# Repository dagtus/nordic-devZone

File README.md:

# nordic-devZone
Share files with support teams

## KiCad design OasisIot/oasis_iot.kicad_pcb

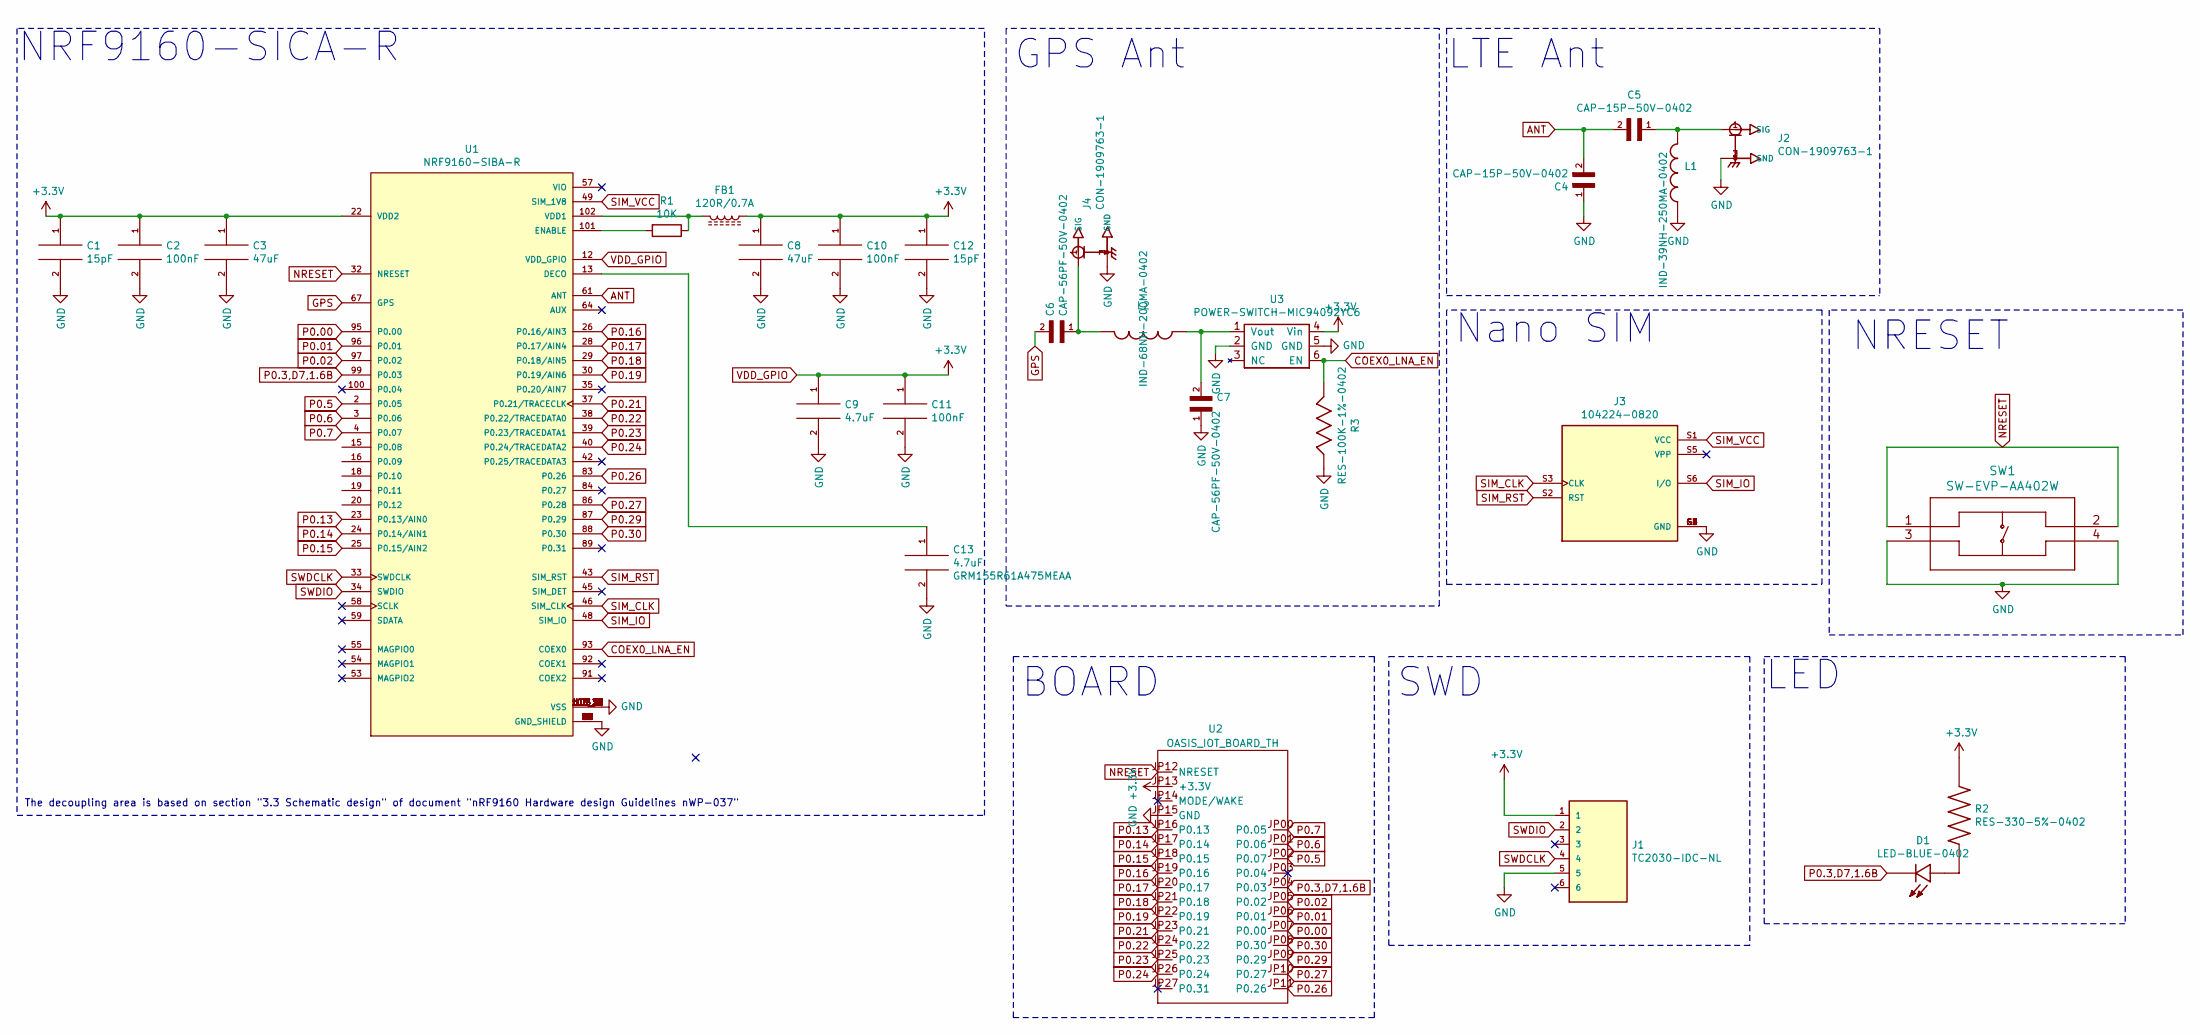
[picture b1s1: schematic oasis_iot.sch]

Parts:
C1, C12: 15pF; C_0201_0603Metric; Part Number GJM0335C1E150JB01
C2, C10, C11: 100nF; C_0201_0603Metric; Part Number GRM033R61A104KE15
C3, C8: 47uF; C_0805_2012Metric; Part Number GRM21BR61A476ME15
C4, C5: CAP-15P-50V-0402; CAPC1005X55N
C6, C7: CAP-56PF-50V-0402; CAPC1005X55N
C9, C13: 4.7uF; C_0402_1005Metric; Part Number GRM155R61A475MEAA
D1: LED-BLUE-0402; EAST10052BA0; PARTREV 3
FB1: 120R/0.7A; L_0402_1005Metric; Part number BLM15AX121SN1
J1: TC2030-IDC-NL; TAG_TC2030-IDC-NL; PARTREV MS
J2, J4: CON-1909763-1; TE_1909763-1
J3: 104224-0820; MOLEX_104224-0820; PARTREV A
L1: IND-39NH-250MA-0402; LQG15HN39NJ02D
L2: IND-68NH-200MA-0402; INDC1005X55N
R1: 10K; R_0201_0603Metric; Part Number RC0201FR-0710KL
R2: RES-330-5%-0402; RC0402JR-07330RL
R3: RES-100K-1%-0402; 0402_RES
SW1: SW-EVP-AA402W; EVPAA402W
U1: NRF9160-SIBA-R; PARTREV v0.7.1
U2: OASIS_IOT_BOARD_TH; MODULE_OASIS_IOT_BOARD_TH
U3: POWER-SWITCH-MIC94092YC6; MIC94092YC6-TR

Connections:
ANT: C4.2, C5.2, U1.61 (ANT)
COEX0_LNA_EN: R3.1, U1.93 (COEX0), U3.6 (EN)
GND: C1.2, C2.2, C3.2, C4.1, C7.1, C8.2, C9.2, C10.2, C11.2, C12.2, C13.2, J1.5, J2.2 (GND), J2.3 (GND), J3.G1 (GND), J3.G2 (GND), J3.G3 (GND), J3.G4 (GND), J3.S4 (GND), J4.2 (GND), J4.3 (GND), L1.2, R3.2, SW1.3, SW1.4, U1.1 (GND_SHIELD), U1.5 (GND_SHIELD), U1.9 (GND_SHIELD), U1.14 (GND_SHIELD), U1.17 (GND_SHIELD), U1.21 (GND_SHIELD), U1.27 (GND_SHIELD), U1.31 (GND_SHIELD), U1.36 (GND_SHIELD), U1.41 (GND_SHIELD), U1.44 (GND_SHIELD), U1.47 (GND_SHIELD), U1.50 (GND_SHIELD), U1.52 (GND_SHIELD), U1.56 (GND_SHIELD), U1.60 (GND_SHIELD), U1.62 (GND_SHIELD), U1.63 (GND_SHIELD), U1.65 (GND_SHIELD), U1.66 (GND_SHIELD), U1.72 (GND_SHIELD), U1.74 (GND_SHIELD), U1.75 (GND_SHIELD), U1.76 (GND_SHIELD), U1.77 (GND_SHIELD), U1.78 (GND_SHIELD), U1.79 (GND_SHIELD), U1.80 (GND_SHIELD), U1.81 (GND_SHIELD), U1.82 (GND_SHIELD), U1.85 (GND_SHIELD), U1.90 (GND_SHIELD), U1.94 (GND_SHIELD), U1.98 (GND_SHIELD), U1.103_1 (VSS), U1.103_2 (VSS), U1.103_3 (VSS), U1.103_4 (VSS), U1.103_5 (VSS), U1.103_6 (VSS), U1.103_7 (VSS), U1.103_8 (VSS), U1.103_9 (VSS), U1.103_10 (VSS), U1.103_11 (VSS), U1.103_12 (VSS), U1.103_13 (VSS), U1.103_14 (VSS), U1.103_15 (VSS), U1.103_16 (VSS), U1.103_17 (VSS), U1.103_18 (VSS), U1.103_19 (VSS), U1.103_20 (VSS), U1.103_21 (VSS), U1.103_22 (VSS), U1.103_23 (VSS), U1.103_24 (VSS), U1.103_25 (VSS), U1.103_26 (VSS), U1.103_27 (VSS), U1.103_28 (VSS), U1.103_29 (VSS), U1.103_30 (VSS), U1.103_31 (VSS), U1.103_32 (VSS), U1.103_33 (VSS), U1.103_34 (VSS), U1.103_35 (VSS), U2.JP15 (GND), U3.2 (GND), U3.5 (GND)
GPS: C6.2, U1.67 (GPS)
NRESET: SW1.1, SW1.2, U1.32 (NRESET), U2.JP12 (NRESET)
unnamed: C5.1, J2.1 (SIG), L1.1
unnamed: C6.1, J4.1 (SIG), L2.1
unnamed: C7.2, L2.2, U3.1 (Vout)
unnamed: C13.1, U1.13 (DECO)
unnamed: D1.A, R2.2
unnamed: FB1.2, R1.1, U1.102 (VDD1)
unnamed: R1.2, U1.101 (ENABLE)
P0.00: U1.95 (P0.00), U2.JP07 (P0.00)
P0.01: U1.96 (P0.01), U2.JP06 (P0.01)
P0.02: U1.97 (P0.02), U2.JP05 (P0.02)
P0.3,D7,1.6B: D1.C, U1.99 (P0.03), U2.JP04 (P0.03)
P0.5: U1.2 (P0.05), U2.JP02 (P0.07)
P0.6: U1.3 (P0.06), U2.JP01 (P0.06)
P0.7: U1.4 (P0.07), U2.JP00 (P0.05)
P0.13: U1.23 (P0.13/AIN0), U2.JP16 (P0.13)
P0.14: U1.24 (P0.14/AIN1), U2.JP17 (P0.14)
P0.15: U1.25 (P0.15/AIN2), U2.JP18 (P0.15)
P0.16: U1.26 (P0.16/AIN3), U2.JP19 (P0.16)
P0.17: U1.28 (P0.17/AIN4), U2.JP20 (P0.17)
P0.18: U1.29 (P0.18/AIN5), U2.JP21 (P0.18)
P0.19: U1.30 (P0.19/AIN6), U2.JP22 (P0.19)
P0.21: U1.37 (P0.21/TRACECLK), U2.JP23 (P0.21)
P0.22: U1.38 (P0.22/TRACEDATA0), U2.JP24 (P0.22)
P0.23: U1.39 (P0.23/TRACEDATA1), U2.JP25 (P0.23)
P0.24: U1.40 (P0.24/TRACEDATA2), U2.JP26 (P0.24)
P0.26: U1.83 (P0.26), U2.JP11 (P0.26)
P0.27: U1.86 (P0.28), U2.JP10 (P0.27)
P0.29: U1.87 (P0.29), U2.JP09 (P0.29)
P0.30: U1.88 (P0.30), U2.JP08 (P0.30)
SIM_CLK: J3.S3 (CLK), U1.46 (SIM_CLK)
SIM_IO: J3.S6 (I/O), U1.48 (SIM_IO)
SIM_RST: J3.S2 (RST), U1.43 (SIM_RST)
SIM_VCC: J3.S1 (VCC), U1.49 (SIM_1V8)
SWDCLK: J1.4, U1.33 (SWDCLK)
SWDIO: J1.2, U1.34 (SWDIO)
VDD_GPIO: C1.1, C2.1, C3.1, C8.1, C9.1, C10.1, C11.1, C12.1, FB1.1, J1.1, R2.1, U1.12 (VDD_GPIO), U1.22 (VDD2), U2.JP13 (+3.3V), U3.4 (Vin)

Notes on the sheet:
NRF9160-SICA-R
LTE Ant
GPS Ant
The decoupling area is based on section "3.3 Schematic design" of document "nRF9160 Hardware design Guidelines nWP-037"
Nano SIM
NRESET
BOARD
SWD
LED

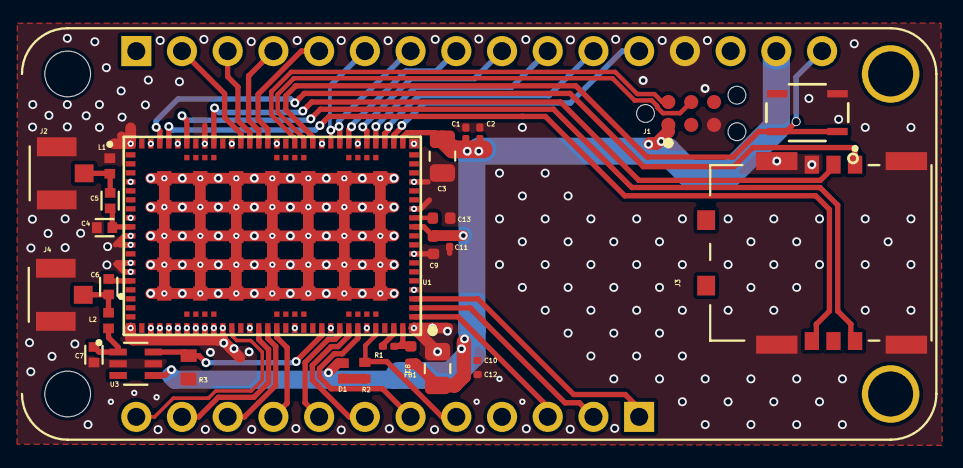
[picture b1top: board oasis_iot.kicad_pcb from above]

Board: 2 copper layers, 28 parts (0 on the bottom side), 41 nets.

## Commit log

2020-11-19 K_TIMER()-HARD_FAULT - Data Access Violation - nrf9160
2020-11-19 Update timer.c
    Adding second options in int_timer,
2020-11-19 Update timer.c
    fixing comment.
2021-06-29 Adding OasisIot project
2021-07-01 Updating ground plane
2021-07-01 Removing old project
